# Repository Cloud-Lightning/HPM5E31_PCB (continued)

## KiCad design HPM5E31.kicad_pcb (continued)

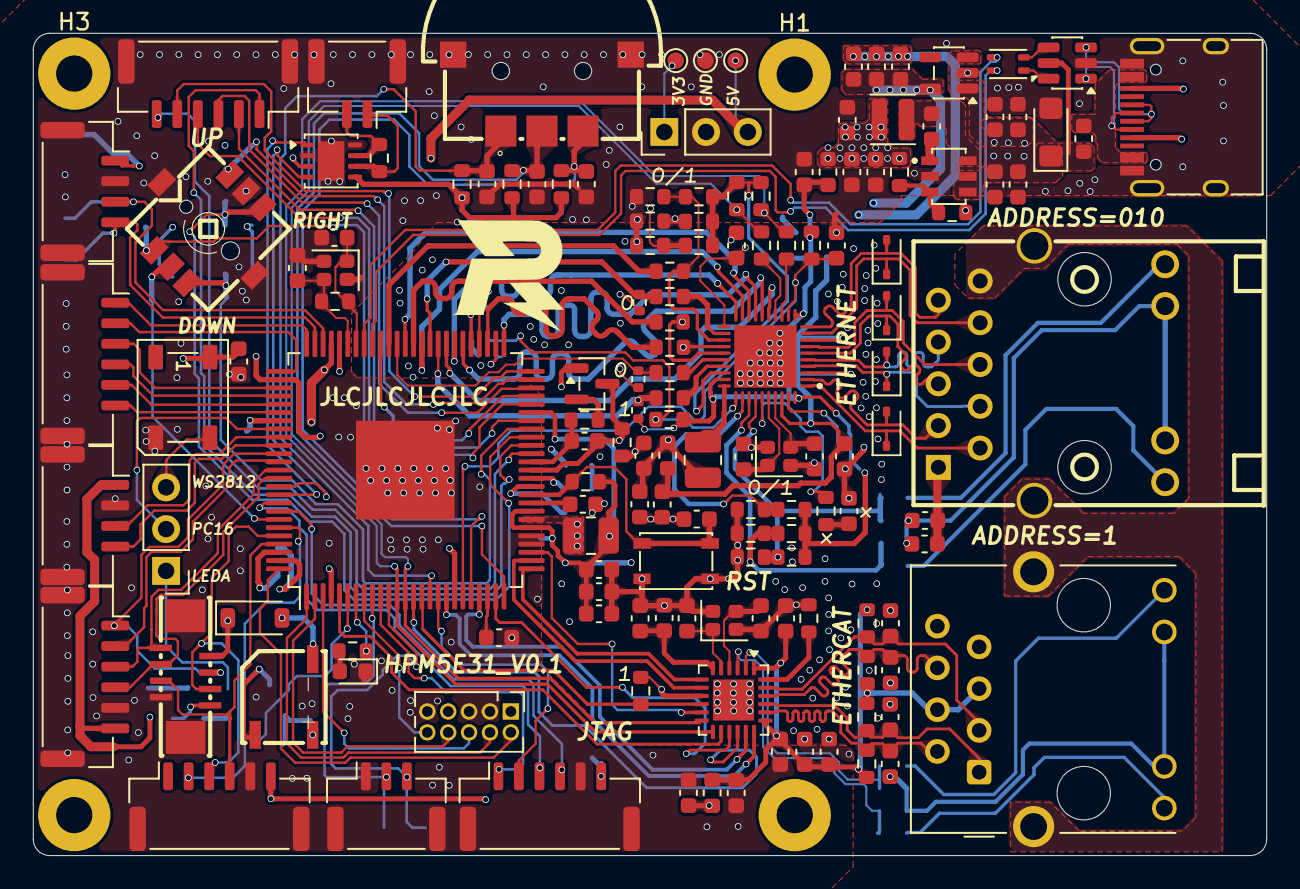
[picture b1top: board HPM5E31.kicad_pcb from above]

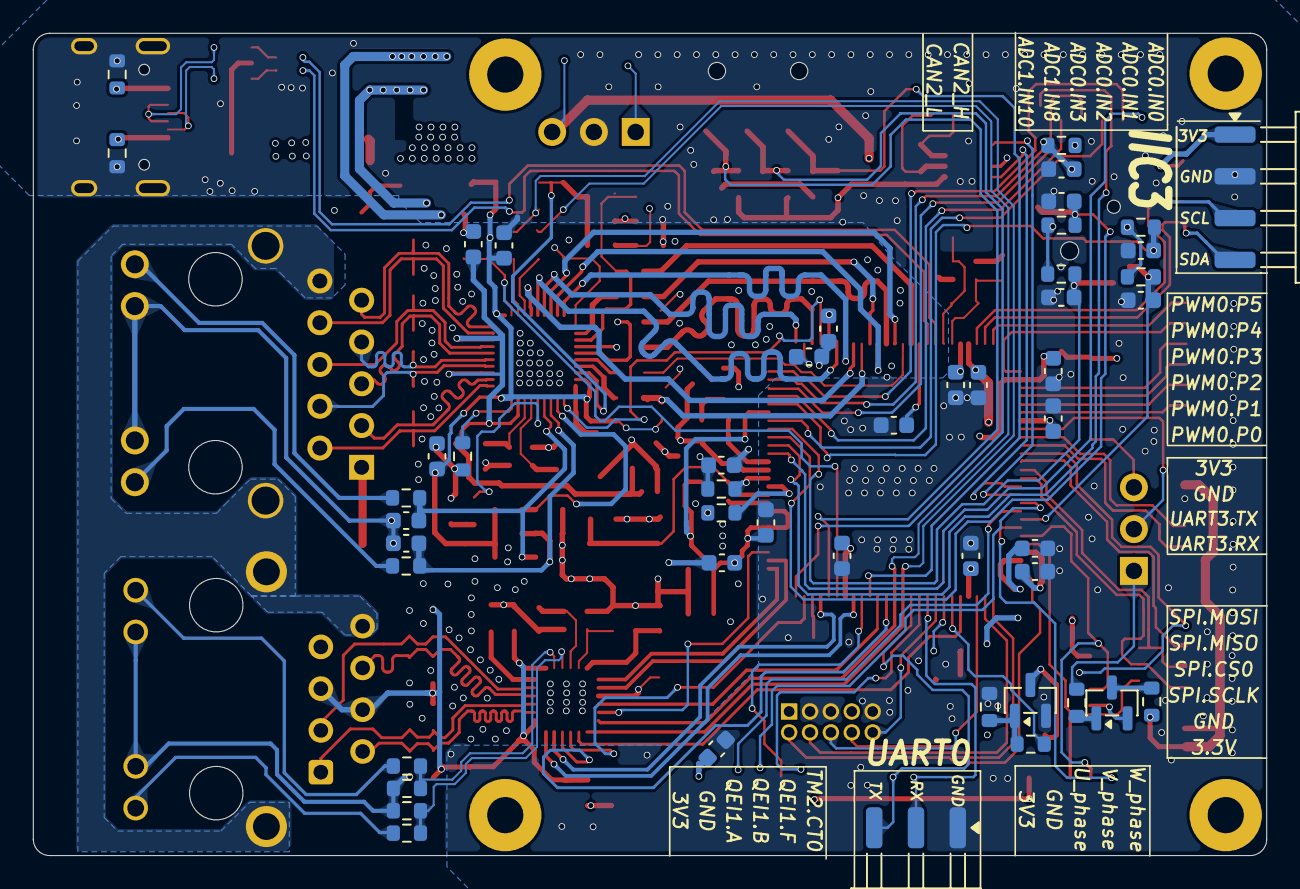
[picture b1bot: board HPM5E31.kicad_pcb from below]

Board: 4 copper layers, 75.0 x 50.0 mm, 198 parts (49 on the bottom side), 157 nets.

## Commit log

2026-03-27 finish
2026-04-04 demo第一版
2026-04-04 modify silkscreen printing
2026-04-09 add pin description
2026-04-15 修改错误引脚
